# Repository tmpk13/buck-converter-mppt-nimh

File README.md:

# MPPT Buck Converter — NiMH D-Cell Charger

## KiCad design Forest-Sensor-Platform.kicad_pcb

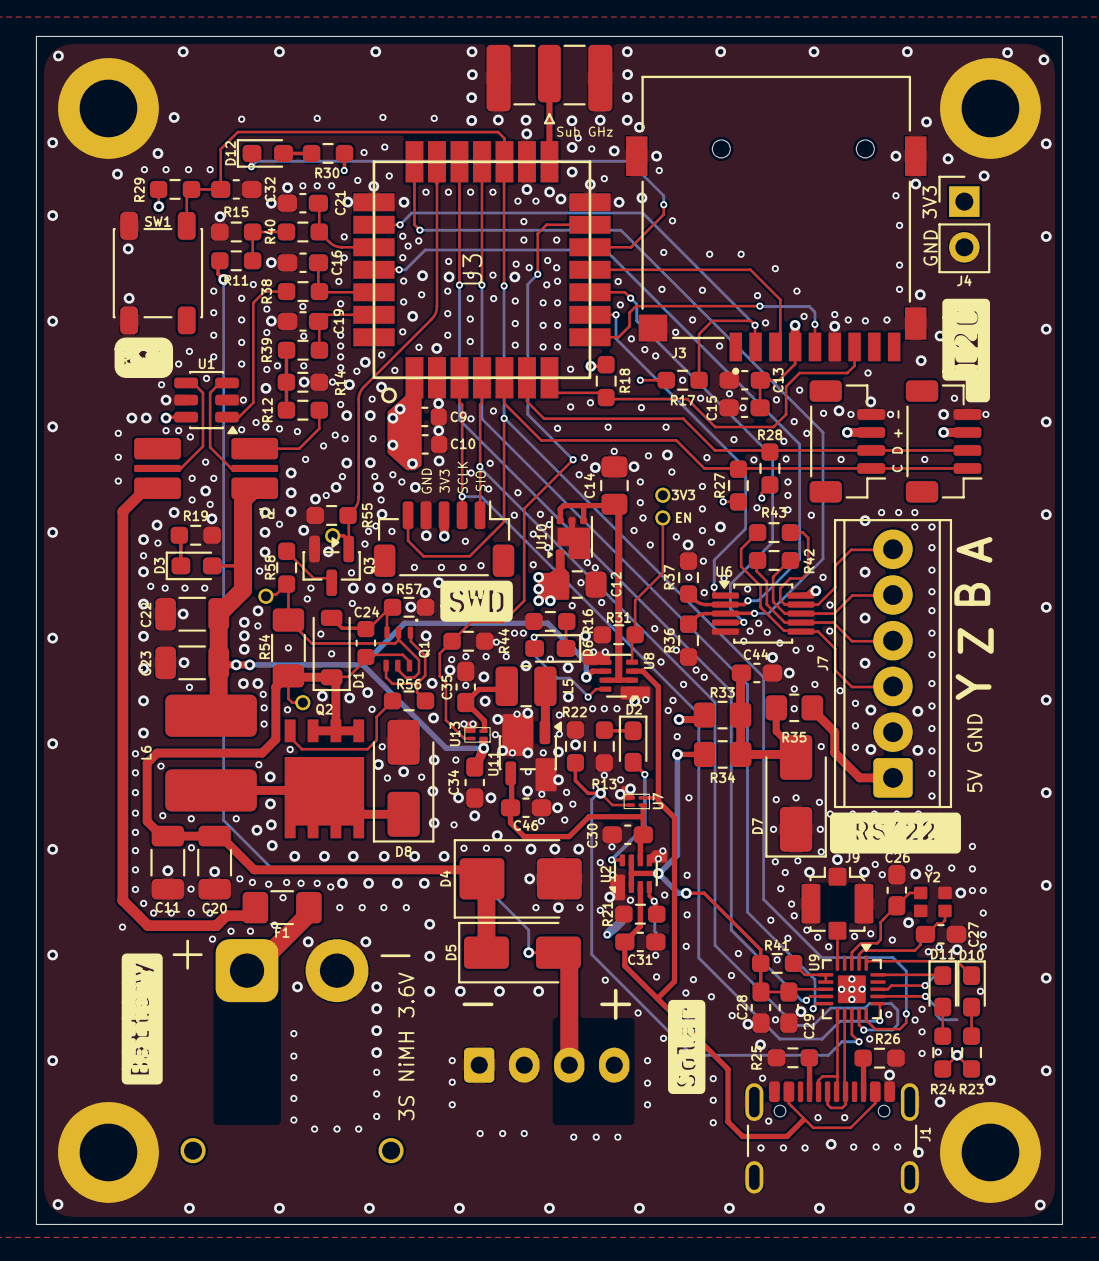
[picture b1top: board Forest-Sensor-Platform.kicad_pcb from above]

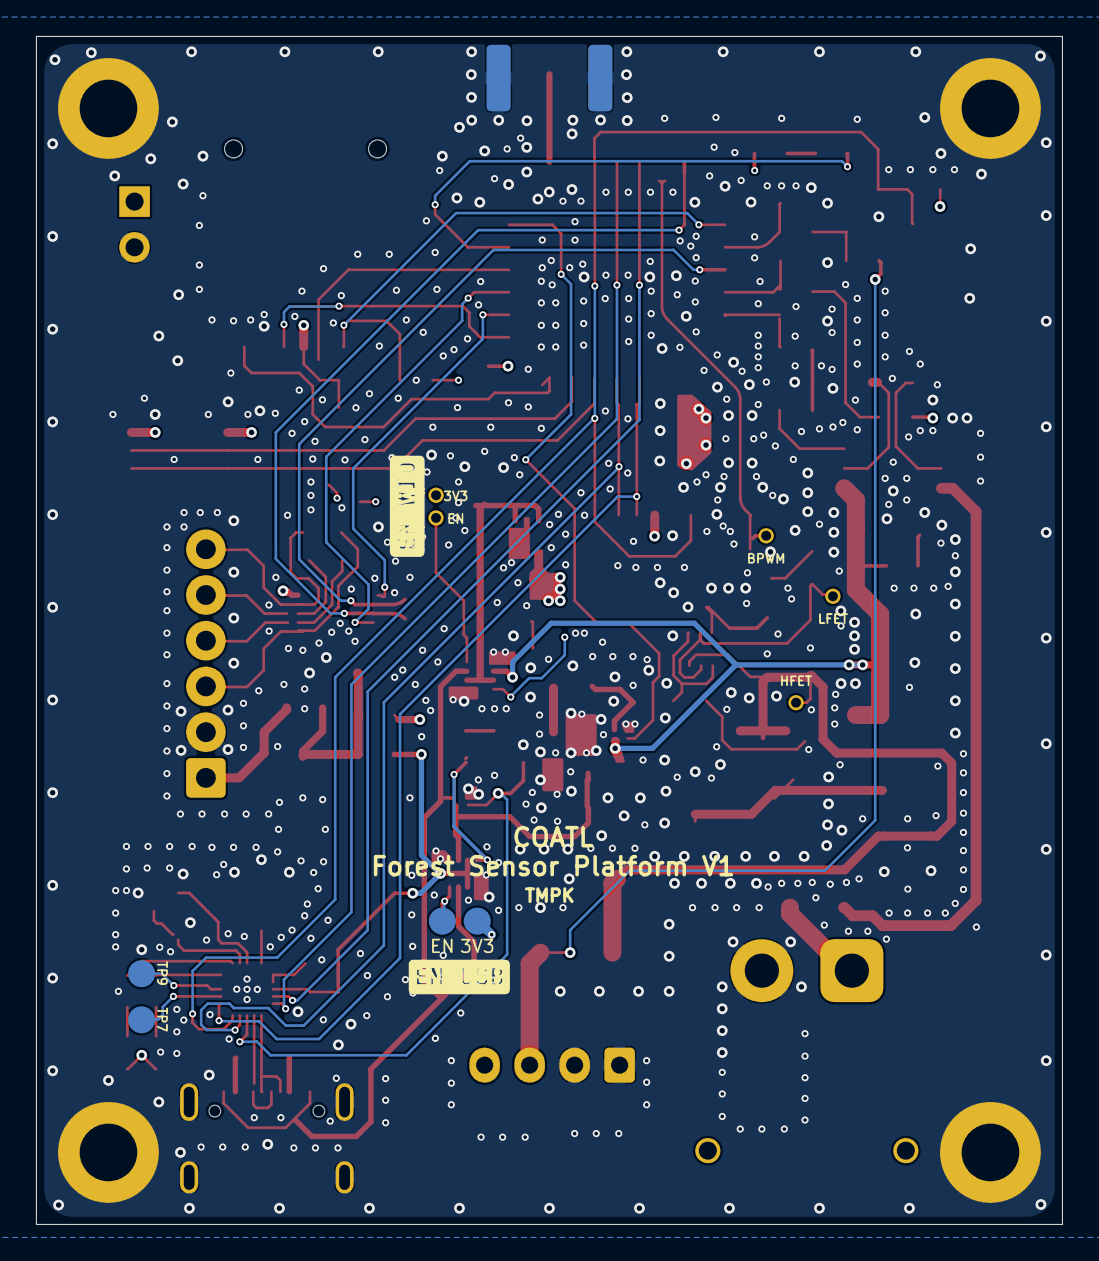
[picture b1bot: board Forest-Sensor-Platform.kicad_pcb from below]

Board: 4 copper layers, 57.0 x 66.0 mm, 116 parts (4 on the bottom side), 75 nets.

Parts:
C9: 10uF 25V; C_0603_1608Metric
C10: 100nF 50V; C_0603_1608Metric
C11, C20: 10uF 50V; C_1206_3216Metric
C12, C14: 1uF 25V; C_0805_2012Metric_Pad1.18x1.45mm_HandSolder
C13, C31, C35: 10uF 25V; C_0603_1608Metric_Pad1.08x0.95mm_HandSolder
C15, C16, C19, C21, C32, C44: 100nF 50V; C_0603_1608Metric_Pad1.08x0.95mm_HandSolder
C22, C23: 47uF 10V; C_1206_3216Metric
C24: 1uF 50V; C_0603_1608Metric
C26, C27: 18p; C_0603_1608Metric_Pad1.08x0.95mm_HandSolder
C28: 2.2u; C_0603_1608Metric_Pad1.08x0.95mm_HandSolder
C29: 100n; C_0603_1608Metric_Pad1.08x0.95mm_HandSolder
C30: 1uF 25V; C_0603_1608Metric_Pad1.08x0.95mm_HandSolder
C34: 1u; C_0603_1608Metric_Pad1.08x0.95mm_HandSolder
C46: 22uF 16V; C_0603_1608Metric_Pad1.08x0.95mm_HandSolder
D1: BZT52B12 12 V 500 mW; D_SOD-123
D2, D3, D6, D10, D11, D12: LED; LED_0603_1608Metric_Pad1.05x0.95mm_HandSolder
D4: SMBJ43A; D_SMB
D5, D8: SK56A 60V 5A SMA; D_SMA
D7: SMAJ5.0CA clamp@9.2V; D_SMA
F1: PTC fuse; Fuse_1206_3216Metric_Pad1.42x1.75mm_HandSolder
H1, H2, H3, H4: MountingHole_Pad; MountingHole_3.2mm_M3_DIN965_Pad
J1: USB_C_2.0_16P; USB_C_Receptacle_GCT_USB4105-xx-A_16P_TopMnt_Horizontal
J2: Conn_01x05_Shielded; JST_SH_BM05B-SRSS-TB_1x05-1MP_P1.00mm_Vertical
J3: MSD-1-A; CUI_MSD-1-A
J4: POWER; PinHeader_1x02_P2.54mm_Vertical
J6: Battery XT30; AMASS_XT30PW-M_1x02_P2.50mm_Horizontal
J7: Conn_01x06 2.54mm Screw Terminal; TerminalBlock_Phoenix_MPT-0,5-6-2.54_1x06_P2.54mm_Horizontal
J8: I2C1; JST_SH_BM04B-SRSS-TB_1x04-1MP_P1.00mm_Vertical
J9: U.FL; U.FL_Molex_MCRF_73412-0110_Vertical
J10: I2C2; JST_SH_BM04B-SRSS-TB_1x04-1MP_P1.00mm_Vertical
J14: Solar In; JST_XH_S4B-XH-A-1_1x04_P2.50mm_Horizontal
L5: 2.2uH; L_1008_2520Metric
L6: 33uH lsat@2.5A; SRN6045TA-330M
Q1: MBT3946DW1T2G
Q2: MCAC054P10Y-TP
Q3: BSS123NH6433XTMA1; SOT-23
R1: Shunt 50m Ohm 2512; Shunt_2512
R11, R55: 100K; R_0603_1608Metric_Pad0.98x0.95mm_HandSolder
R12, R13, R14, R15, R16, R17, R18, R23, R24, R29, R30, R57: 10K; R_0603_1608Metric_Pad0.98x0.95mm_HandSolder
R19, R38, R39, R40: 1K; R_0603_1608Metric_Pad0.98x0.95mm_HandSolder
R21, R22, R31, R36, R37, R44: 1M; R_0603_1608Metric_Pad0.98x0.95mm_HandSolder
R25, R26: 5.1K; R_0603_1608Metric_Pad0.98x0.95mm_HandSolder
R27, R28: 4.7K; R_0603_1608Metric_Pad0.98x0.95mm_HandSolder
R33, R34: 0; R_0805_2012Metric_Pad1.20x1.40mm_HandSolder
R35: 100; R_0805_2012Metric_Pad1.20x1.40mm_HandSolder
R41: 1.5K; R_0603_1608Metric_Pad0.98x0.95mm_HandSolder
R42, R43: 0; R_0603_1608Metric_Pad0.98x0.95mm_HandSolder
R54: 4.7K; R_1206_3216Metric_Pad1.30x1.75mm_HandSolder
R56: 22R; R_0603_1608Metric_Pad0.98x0.95mm_HandSolder
R58: 2.2K; R_0603_1608Metric_Pad0.98x0.95mm_HandSolder
SMA1: ANT-SMA; SMA_Samtec_SMA-J-P-H-ST-EM1_EdgeMount
SW1: WIO_RST; SW_SPST_PTS647_Sx38
TP1, TP2, TP7, TP9: TestPoint; Testpad
TP3, TP4, TP5, TP6, TP8: TestPoint; Testhole-1.00mm
U1: INA181A1; SOT-23-6
U2, U8: LM66200DRLR; SOT-583-8
U3: Wio-E5, STM32WLE5 Module; WIO-E5
U6: TPT482-VS2R; MSOP-10_3x3mm_P0.5mm
U7, U13: TPS22991CRAAR
U9: CH572D
U10: TLV75733PDRV; WSON-6-1EP_2x2mm_P0.65mm_EP1x1.6mm
U11: TPS613222ADBV; SOT-23-5
Y2: Crystal_GND2; XRCGB32M000F1S1DR0

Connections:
5V_EN: R44.1, U3.13 (PC0), U13.2 (ON)
+3.3V: C9.1, C10.1, C12.1, C13.1, C15.1, J2.3, J3.4 (VDD), J4.1, J8.3, J10.3, R17.1, R18.1, R23.2, R24.2, R27.1, R28.1, R29.1, R30.2, R33.1, TP2.1 (1_1), TP3.1 (1_1), U1.6 (V+), U3.1 (VCC), U6.10 (VCC), U10.1 (OUT)
+5V: C28.1, C29.2, R34.1, R41.2, U2.2 (VOUT), U2.7 (VOUT), U9.8 (V5)
/Buck Converter/Solar +: D5.2 (A), J14.3, J14.4, R11.1
/Buck Converter/Solar In: C11.1, C20.1, C24.1, D1.1 (K), D4.1 (K), D5.1 (K), Q1.6 (C1), Q2.1 (S), Q2.2 (S), Q2.3 (S), R54.1, TP5.1 (1_1)
/Forest-Sensor-Platform/5V_Boost: C30.1, C46.1, U2.6 (VIN2), U7.1 (VIN), U11.4 (VOUT)
/Forest-Sensor-Platform/5V_SW: L5.2, U11.1 (SW)
/Forest-Sensor-Platform/I2C-1-SCL: J8.1, J10.1, R27.2, U3.5 (PB15)
/Forest-Sensor-Platform/I2C-1-SDA: J8.2, J10.2, R28.2, U3.6 (PA15)
/Forest-Sensor-Platform/PWR-IN: C14.1, U8.2 (VOUT), U8.7 (VOUT), U10.4 (EN), U10.6 (IN)
/Forest-Sensor-Platform/RS422_A: J7.6, R43.1, U6.9 (A)
/Forest-Sensor-Platform/RS422_B: J7.5, R42.1, U6.8 (B)
/Forest-Sensor-Platform/RS422_Y: J7.3, R43.2, U6.6 (Y)
/Forest-Sensor-Platform/RS422_Z: J7.4, R42.2, U6.7 (Z)
/Forest-Sensor-Platform/Receiver_Input_Enable: R37.1, U3.25 (PB9), U6.2 (RE)
/Forest-Sensor-Platform/Receiver_Output_Enable: R36.1, U3.21 (PA9), U6.3 (DE)
/Forest-Sensor-Platform/SPI-CITO: J3.7 (DAT0), R18.2, U3.7 (PB4)
/Forest-Sensor-Platform/SPI-COTI: J3.3 (CMD), U3.11 (PB5)
/Forest-Sensor-Platform/SPI-CS: J3.2 (CD/DAT3), R17.2, U3.23 (PA0)
/Forest-Sensor-Platform/SPI-SCK: J3.5 (CLK), U3.8 (PB3)
/Forest-Sensor-Platform/UART-1-RX: U3.9 (PB7), U6.1 (R)
/Forest-Sensor-Platform/UART-1-TX: U3.10 (PB6), U6.4 (D)
/Forest-Sensor-Platform/WIO_USR_LED: D12.1 (K), U3.12 (PC1)
/USB/CH_GPIO: TP9.1 (1_1), U9.18 (PA11)
/USB/CH_USR_BTN: TP7.1 (1_1), U9.17 (PA10)
BAT_ISENSE: R38.2, U1.1
Battery_Out: C22.1, C23.1, C34.1, D3.2 (A), L6.2, R1.3, R12.1, U8.6 (VIN2), U13.1 (VIN)
D+: J1.A6 (D+), J1.B6 (D+), U9.12 (PA1(D+))
D-: J1.A7 (D-), J1.B7 (D-), U9.11 (PA0(D-))
GND: C9.2, C10.2, C11.2, C12.2, C13.2, C14.2, C15.2, C16.2, C19.2, C20.2, C21.2, C22.2, C23.2, C26.2, C27.2, C28.2, C29.1, C30.2, C31.2, C32.2, C34.2, C35.2, C44.2, C46.2, D4.2 (A), D7.1 (A1), D8.2 (A), H1.1 (1_1), H2.1 (1_1), H3.1 (1_1), H4.1 (1_1), J1.A1 (GND), J1.A12 (GND), J1.B1 (GND), J1.B12 (GND), J1.SH (Shield), J2.4, J3.6 (VSS), J3.G1 (SH_GND), J3.G2 (SH_GND_1), J3.G3 (SH_GND_2), J3.G4 (SH_GND_3), J4.2, J6.2, J7.2, J8.4, J9.2 (Ext), J10.4, J14.1, J14.2, Q3.2 (S), R13.2, R14.2, R15.2, R16.2, R19.2, R21.2, R22.2, R25.2, R26.2, R31.2, R36.2, R37.2, R44.2, R55.2, R57.2, SMA1.2 (Ext), SW1.2, U1.2 (GND), U1.5 (REF), U2.1 (GND), U2.5 (GND), U3.2 (GND), U3.14 (GND), U3.16 (GND), U3.22 (GND), U6.5 (GND), U7.4 (GND), U8.1 (GND), U8.5 (GND), U9.21 (GND), U10.2 (GND), U10.3 (GND), U10.5 (GND), U10.7 (GND), U11.2 (GND), U11.3 (GND), U11.5 (GND), U13.4 (GND), Y2.2
unnamed: C24.2, D1.2 (A), Q1.3 (C2), R57.1
unnamed: D2.2 (A), U2.8 (ST)
unnamed: D2.1 (K), R13.1
unnamed: D3.1 (K), R19.1
unnamed: D6.2 (A), U8.8 (ST)
unnamed: D6.1 (K), R16.1
unnamed: C44.1, D7.2 (A2), R33.2, R34.2, R35.2
unnamed: D8.1 (K), L6.1, Q2.5 (D), Q2.6 (D), Q2.7 (D), Q2.8 (D)
unnamed: D10.2 (A), R23.1
unnamed: D10.1 (K), U9.1 (PA3)
unnamed: D11.2 (A), R24.1
unnamed: D11.1 (K), U9.20 (PA2)
unnamed: D12.2 (A), R30.1
unnamed: F1.1, R1.1
unnamed: J1.A5 (CC1), R25.1
unnamed: J1.B5 (CC2), R26.1
unnamed: F1.2, J6.1
unnamed: J7.1, R35.1
unnamed: J9.1 (In), U9.5 (ANT)
unnamed: Q1.2 (B1), Q1.5 (B2), R54.2, R58.1, TP6.1 (1_1)
unnamed: Q1.1 (E1), Q1.4 (E2), R56.2
unnamed: Q2.4 (G), R56.1
unnamed: Q3.3 (D), R58.2
unnamed: SMA1.1 (In), U3.15 (RFIO)
unnamed: R1.4, U1.3 (+)
unnamed: R1.2, U1.4 (-)
unnamed: R21.1, TP1.1 (1_1), U2.4 (~ON)
unnamed: C19.1, R39.1, U3.27 (PA10)
unnamed: C21.1, R40.1, U3.24 (PB13)
unnamed: C16.1, R38.1, U3.26 (PB14)
unnamed: R31.1, TP4.1 (1_1), U8.4 (~ON)
unnamed: R41.1, U9.6 (VDD3), U9.7 (VIO)
unnamed: C26.1, U9.3 (XI), Y2.3
unnamed: C27.1, U9.2 (XO), Y2.1
unnamed: C35.1, L5.1, U13.3 (VOUT)
PWM_Buck: Q3.1 (G), R55.1, TP8.1 (1_1), U3.20 (PB10)
SWD-WIO-CLK: J2.1, U3.4 (PA14), U9.14 (PA5)
SWD-WIO-IO: J2.2, U3.3 (PA13), U9.16 (PA7)
UART-WIO-RX: U3.18 (PA3), U9.10 (PA8)
UART-WIO-TX: U3.19 (PA2), U9.9 (PA9)
USB_VOUT_EN: R22.1, U7.2 (ON), U9.13 (PA4)
VSENSE_OUT: R12.2, R14.1, R39.2
VSENSE_VIN: R11.2, R15.1, R40.2
VUSB: C31.1, J1.A4 (VBUS), J1.A9 (VBUS), J1.B4 (VBUS), J1.B9 (VBUS), U2.3 (VIN1), U7.3 (VOUT), U8.3 (VIN1)
WIO-RST: C32.1, J2.5, R29.2, SW1.1, U3.17 (RST), U9.15 (PA6)

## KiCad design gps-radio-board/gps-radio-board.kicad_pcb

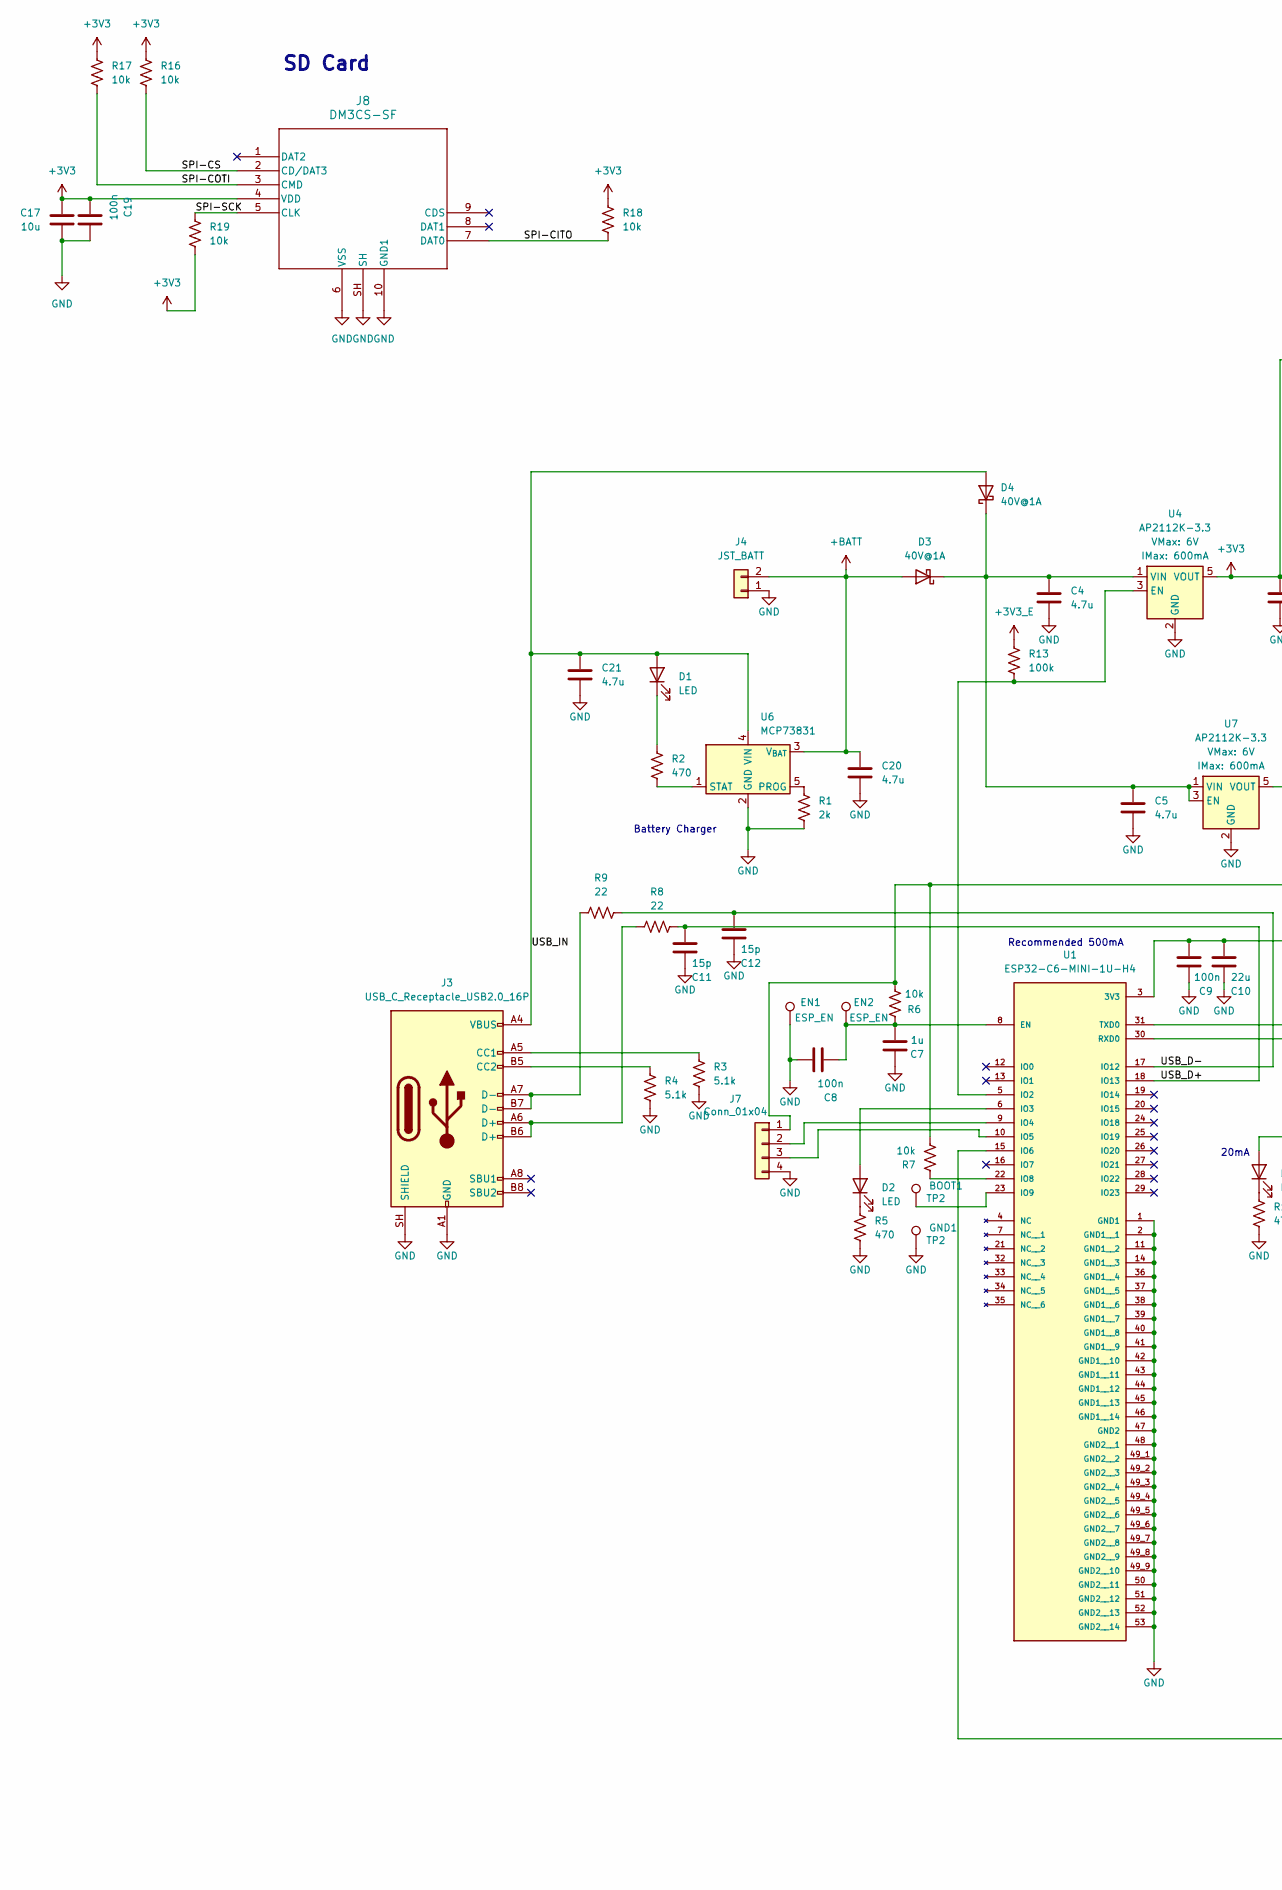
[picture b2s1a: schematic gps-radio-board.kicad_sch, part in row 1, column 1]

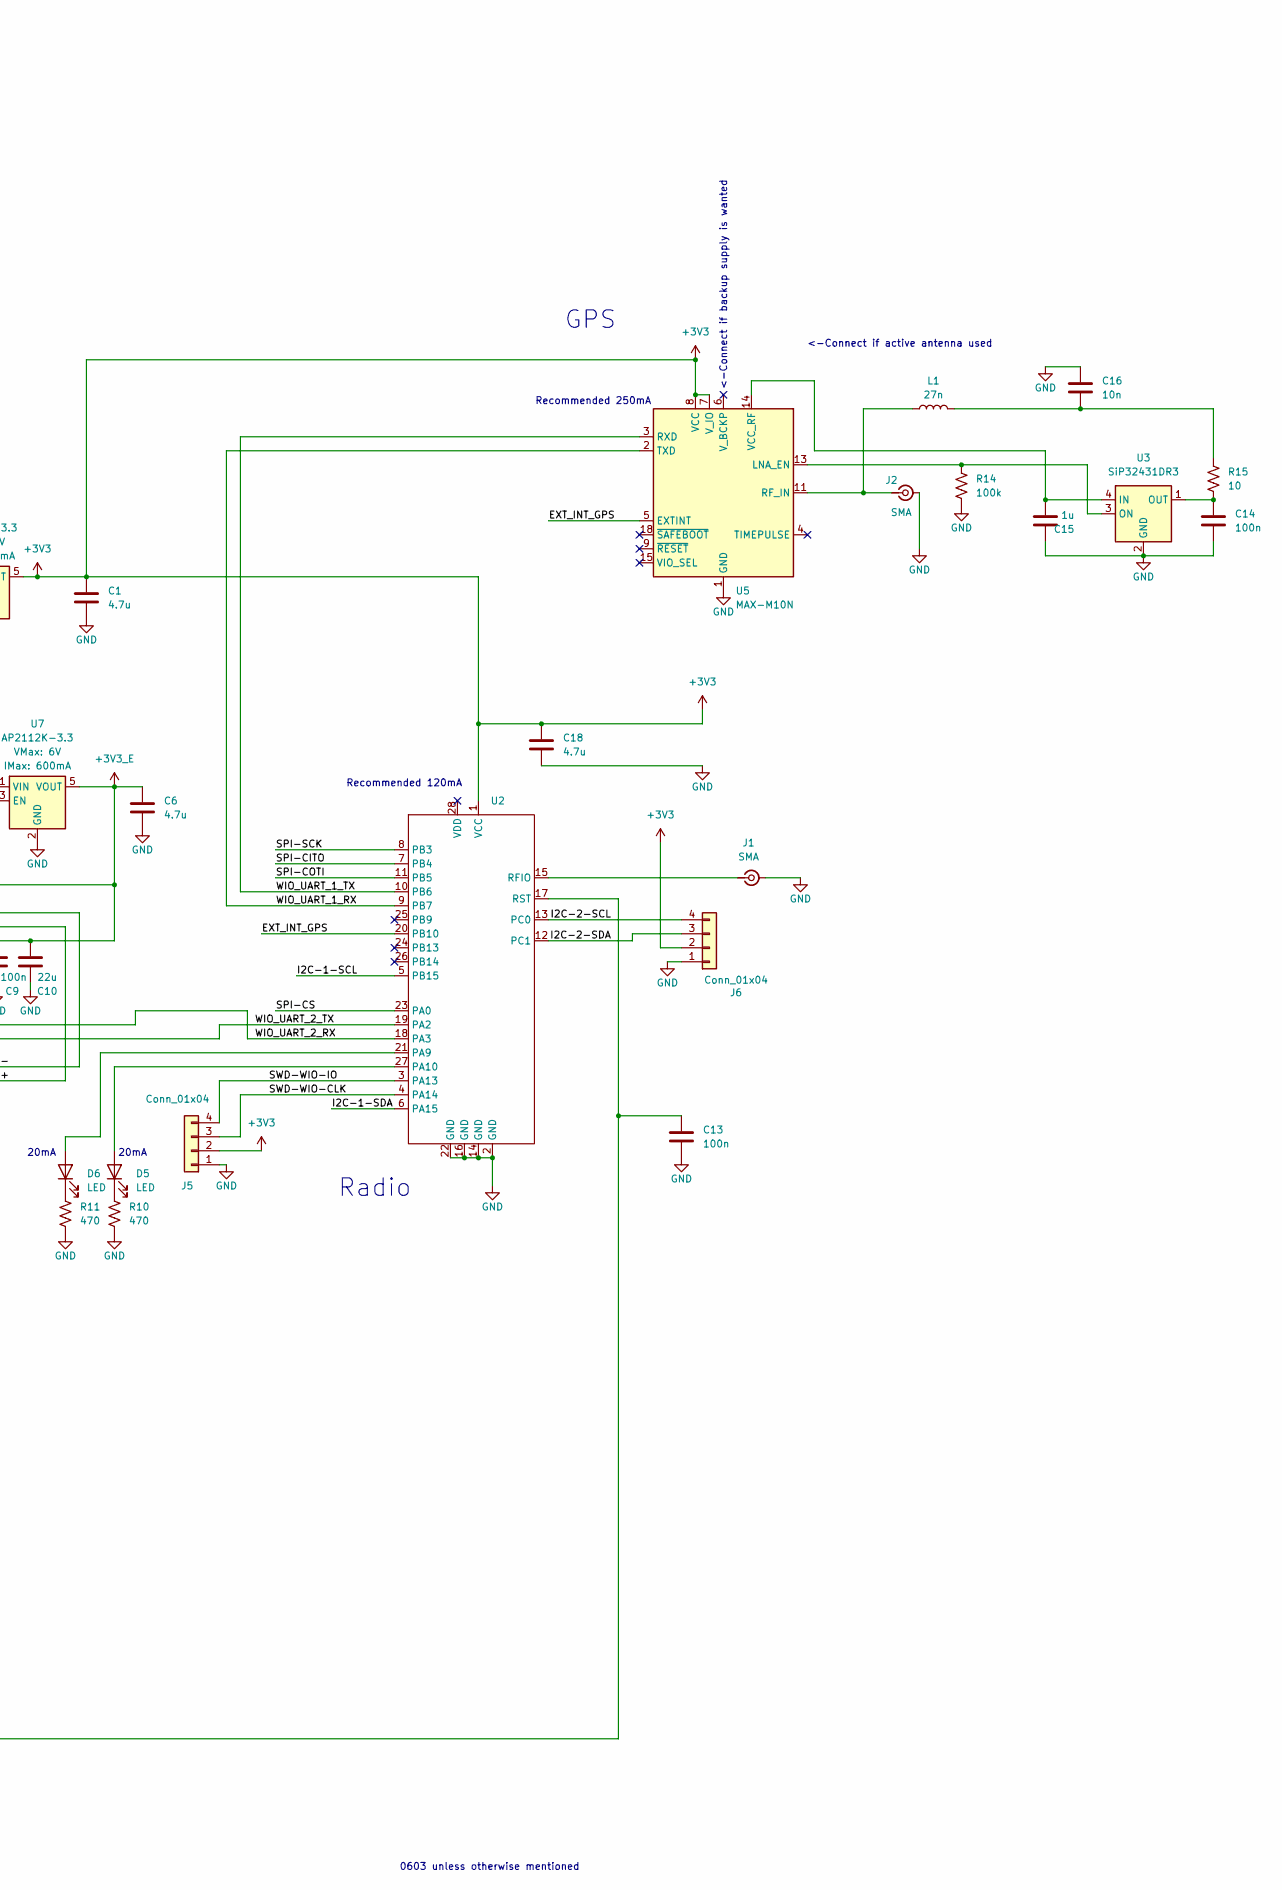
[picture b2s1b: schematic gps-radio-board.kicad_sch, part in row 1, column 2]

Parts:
BOOT1: TP2; TestPoint_Pad_1.0x1.0mm
C1, C4, C5, C6, C18, C20, C21: 4.7u; C_0603_1608Metric_Pad1.08x0.95mm_HandSolder
C7, C15: 1u; C_0603_1608Metric_Pad1.08x0.95mm_HandSolder
C8, C9, C13, C14, C19: 100n; C_0603_1608Metric_Pad1.08x0.95mm_HandSolder
C10: 22u; C_0603_1608Metric_Pad1.08x0.95mm_HandSolder
C11, C12: 15p; C_0603_1608Metric_Pad1.08x0.95mm_HandSolder
C16: 10n; C_0603_1608Metric_Pad1.08x0.95mm_HandSolder
C17: 10u; C_0603_1608Metric_Pad1.08x0.95mm_HandSolder
D1, D2, D5, D6: LED; LED_0603_1608Metric_Pad1.05x0.95mm_HandSolder
D3, D4: 40V@1A; D_SOD-123
EN1, EN2: ESP_EN; TestPoint_Pad_1.0x1.0mm
GND1: TP2; TestPoint_Pad_1.0x1.0mm
J1, J2: SMA; SMA_Amphenol_132289_EdgeMount
J3: USB_C_Receptacle_USB2.0_16P; USB_C_Receptacle_GCT_USB4105-xx-A_16P_TopMnt_Horizontal
J4: JST_BATT; JST_GH_SM02B-GHS-TB_1x02-1MP_P1.25mm_Horizontal
J5, J6: Conn_01x04; JST_SH_BM04B-SRSS-TB_1x04-1MP_P1.00mm_Vertical
J7: Conn_01x04; PinHeader_1x04_P2.54mm_Vertical
J8: DM3CS-SF; microSD_HC_Hirose_DM3D-SF
L1: 27n; L_0402_1005Metric_Pad0.77x0.64mm_HandSolder
R1: 2k; R_0603_1608Metric_Pad0.98x0.95mm_HandSolder
R2, R5, R10, R11: 470; R_0603_1608Metric_Pad0.98x0.95mm_HandSolder
R3, R4: 5.1k; R_0603_1608Metric_Pad0.98x0.95mm_HandSolder
R6, R7, R16, R17, R18, R19: 10k; R_0603_1608Metric_Pad0.98x0.95mm_HandSolder
R8, R9: 22; R_0603_1608Metric_Pad0.98x0.95mm_HandSolder
R13, R14: 100k; R_0603_1608Metric_Pad0.98x0.95mm_HandSolder
R15: 10; R_0603_1608Metric_Pad0.98x0.95mm_HandSolder
U1: ESP32-C6-MINI-1U-H4; XCVR_ESP32-C6-MINI-1U-H4; PARTREV 1.0
U2: LoRa-E5
U3: SiP32431DR3; SOT-363_SC-70-6
U4, U7: AP2112K-3.3; SOT23-5
U5: MAX-M10N; ublox_MAX
U6: MCP73831; SOT-23-5_HandSoldering

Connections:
+3V3: C1.1, C17.2, C18.1, C19.1, J5.2, J6.2, J8.4 (VDD), R16.2, R17.2, R18.2, R19.1, U2.1 (VCC), U4.5 (VOUT), U5.7 (V_IO), U5.8 (VCC)
+3V3_E: C6.1, C9.2, C10.2, J7.1, R6.2, R7.2, R13.2, U1.3 (3V3), U7.5 (VOUT)
+BATT: C20.1, D3.2 (A), J4.2, U6.3 (V_{BAT})
/EXT_INT_GPS: U2.20 (PB10), U5.5 (EXTINT)
/I2C-1-SCL: U2.5 (PB15)
/I2C-1-SDA: U2.6 (PA15)
/I2C-2-SCL: J6.4, U2.13 (PC0)
/I2C-2-SDA: J6.3, U2.12 (PC1)
/SPI-CITO: J8.7 (DAT0), R18.1, U2.7 (PB4)
/SPI-COTI: J8.3 (CMD), R17.1, U2.11 (PB5)
/SPI-CS: J8.2 (CD/DAT3), R16.1, U2.23 (PA0)
/SPI-SCK: J8.5 (CLK), R19.2, U2.8 (PB3)
/SWD-WIO-CLK: J5.3, U2.4 (PA14)
/SWD-WIO-IO: J5.4, U2.3 (PA13)
/USB_D+: C11.2, R8.1, U1.18 (IO13)
/USB_D-: C12.2, R9.1, U1.17 (IO12)
/USB_IN: C21.1, D1.2 (A), D4.2 (A), J3.A4 (VBUS), J3.A9 (VBUS), J3.B4 (VBUS), J3.B9 (VBUS), U6.4 (VIN)
/WIO_UART_1_RX: U2.9 (PB7), U5.2 (TXD)
/WIO_UART_1_TX: U2.10 (PB6), U5.3 (RXD)
/WIO_UART_2_RX: U1.31 (TXD0), U2.18 (PA3)
/WIO_UART_2_TX: U1.30 (RXD0), U2.19 (PA2)
GND: C1.2, C4.2, C5.2, C6.2, C7.1, C8.2, C9.1, C10.1, C11.1, C12.1, C13.2, C14.2, C15.1, C16.1, C17.1, C18.2, C19.2, C20.2, C21.2, EN1.1 (1_1), GND1.1 (1_1), J1.2 (Ext), J2.2 (Ext), J3.A1 (GND), J3.A12 (GND), J3.B1 (GND), J3.B12 (GND), J3.SH (SHIELD), J4.1, J5.1, J6.1, J7.4, J8.6 (VSS), J8.10 (GND1), J8.SH, R1.2, R3.2, R4.2, R5.2, R10.2, R11.2, R14.1, U1.1 (GND1), U1.2 (GND1__1), U1.11 (GND1__2), U1.14 (GND1__3), U1.36 (GND1__4), U1.37 (GND1__5), U1.38 (GND1__6), U1.39 (GND1__7), U1.40 (GND1__8), U1.41 (GND1__9), U1.42 (GND1__10), U1.43 (GND1__11), U1.44 (GND1__12), U1.45 (GND1__13), U1.46 (GND1__14), U1.47 (GND2), U1.48 (GND2__1), U1.49_1 (GND2__2), U1.49_2 (GND2__3), U1.49_3 (GND2__4), U1.49_4 (GND2__5), U1.49_5 (GND2__6), U1.49_6 (GND2__7), U1.49_7 (GND2__8), U1.49_8 (GND2__9), U1.49_9 (GND2__10), U1.50 (GND2__11), U1.51 (GND2__12), U1.52 (GND2__13), U1.53 (GND2__14), U2.2 (GND), U2.14 (GND), U2.16 (GND), U2.22 (GND), U3.2 (GND), U3.5 (GND), U4.2 (GND), U5.1 (GND), U5.10 (GND), U5.12 (GND), U6.2 (GND), U7.2 (GND)
unnamed: C16.2, L1.2, R15.2
unnamed: D1.1 (K), R2.1
unnamed: D2.2 (A), U1.6 (IO3)
unnamed: D2.1 (K), R5.1
unnamed: C4.1, C5.1, D3.1 (K), D4.1 (K), U4.1 (VIN), U7.1 (VIN), U7.3 (EN)
unnamed: D5.2 (A), U2.27 (PA10)
unnamed: D5.1 (K), R10.1
unnamed: D6.2 (A), U2.21 (PA9)
unnamed: D6.1 (K), R11.1
unnamed: J1.1 (In), U2.15 (RFIO)
unnamed: J2.1 (In), L1.1, U5.11 (RF_IN)
unnamed: J3.A5 (CC1), R3.1
unnamed: J3.B5 (CC2), R4.1
unnamed: J3.A6 (D+), J3.B6 (D+), R8.2
unnamed: J3.A7 (D-), J3.B7 (D-), R9.2
unnamed: J7.2, U1.9 (IO4)
unnamed: J7.3, U1.10 (IO5)
unnamed: C7.2, C8.1, EN2.1 (1_1), R6.1, U1.8 (EN)
unnamed: R13.1, U1.5 (IO2), U4.3 (EN)
unnamed: C13.1, U1.15 (IO6), U2.17 (RST)
unnamed: R7.1, U1.22 (IO8)
unnamed: BOOT1.1 (1_1), U1.23 (IO9)
unnamed: C15.2, U3.4 (IN), U5.14 (VCC_RF)
unnamed: R14.2, U3.3 (ON), U5.13 (LNA_EN)
unnamed: C14.1, R15.1, U3.1 (OUT)
unnamed: R1.1, U6.5 (PROG)
unnamed: R2.2, U6.1 (STAT)

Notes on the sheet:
Radio
<-Connect if active antenna used
0603 unless otherwise mentioned
20mA
Recommended 120mA
SD Card
<-Connect if backup supply is wanted
Recommended 500mA
GPS
Recommended 250mA
Battery Charger

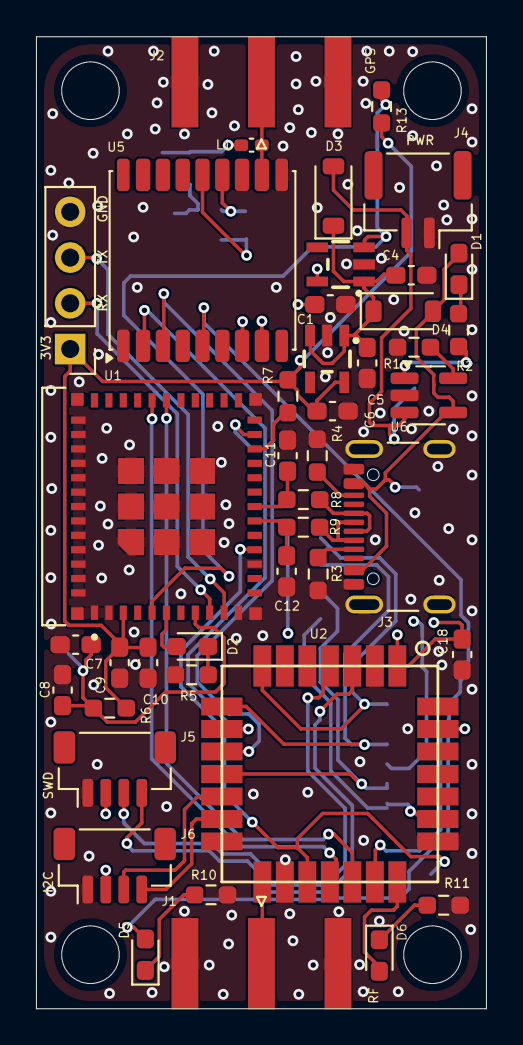
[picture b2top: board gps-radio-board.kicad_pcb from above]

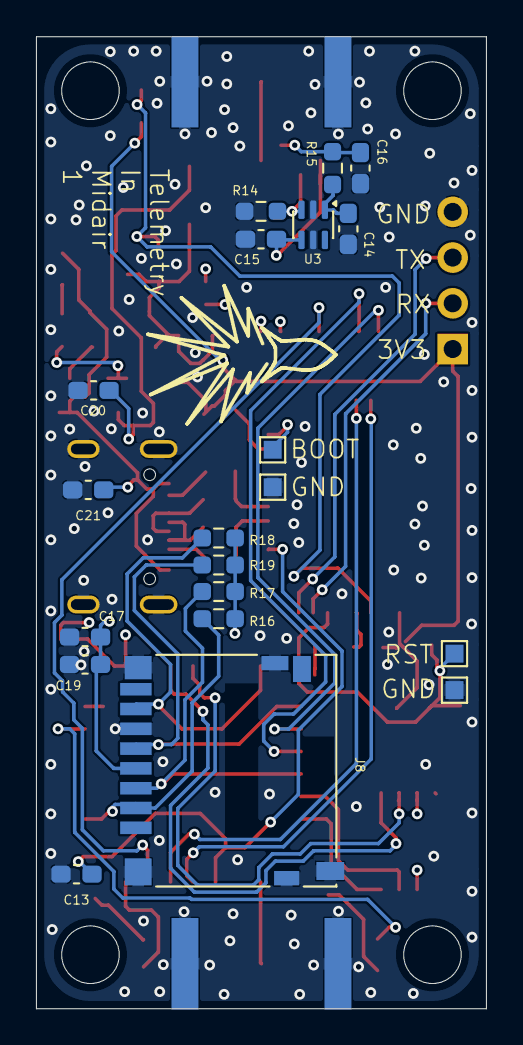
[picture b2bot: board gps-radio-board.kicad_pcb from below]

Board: 4 copper layers, 25.0 x 54.0 mm, 63 parts (20 on the bottom side), 47 nets.

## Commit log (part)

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2026-03-30 Add local files
2026-04-05 Add layout and new components
2026-04-05 Add update plot for new components
2026-04-05 Add update plot for component values
2026-04-20 Update PCB
2026-04-21 Update PCB routing
2026-04-21 Add image
2026-04-21 Add image to readme
